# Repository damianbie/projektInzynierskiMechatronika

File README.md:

# Projekt Inżynierski z Mechatroniki

## struktura katalogów

- raport - raport projektu
- algorytm - implementacją algorytmu A i środowiska testowewgo
- robot - projekt fizycznego rogota
    - cady - proejkt cad robota
    - pcbV2 - projekt płytki w programie kiCad
    - soft - oprogramowanie robota napisane w C++ i IDF4.4

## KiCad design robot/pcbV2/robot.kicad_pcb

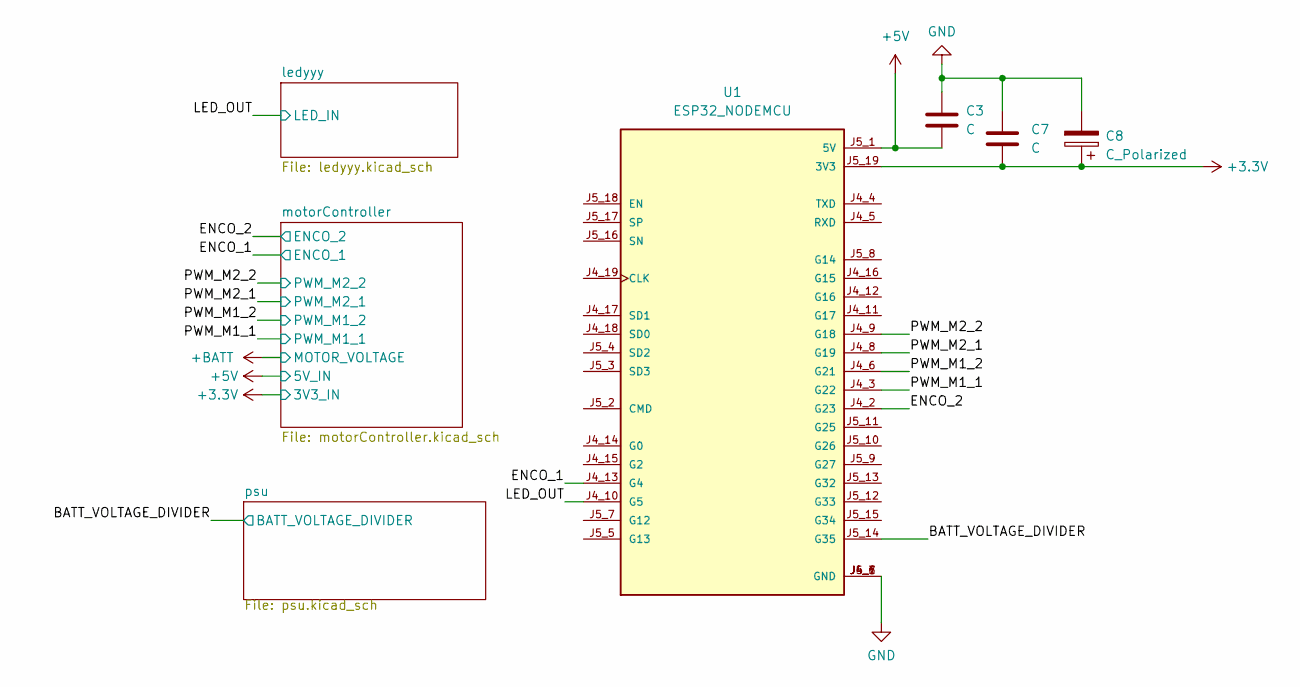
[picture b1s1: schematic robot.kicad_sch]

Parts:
C3, C7: C; C_1210_3225Metric
C8: C_Polarized; CP_Elec_6.3x7.7
U1: ESP32_NODEMCU; MODULE_ESP32_NODEMCU

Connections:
+3.3V: C7.2, C8.1, U1.J5_19 (3V3); also elsewhere on the board
+5V: C3.2, U1.J5_1 (5V); also elsewhere on the board
-BATT: C3.1, C7.1, C8.2, U1.J4_1 (GND), U1.J4_7 (GND), U1.J5_6 (GND); also elsewhere on the board
/BATT_VOLTAGE_DIVIDER: U1.J5_14 (G35); also elsewhere on the board
/ENCO_1: U1.J4_13 (G4); also elsewhere on the board
/ENCO_2: U1.J4_2 (G23); also elsewhere on the board
/LED_OUT: U1.J4_10 (G5); also elsewhere on the board
/PWM_M1_1: U1.J4_3 (G22); also elsewhere on the board
/PWM_M1_2: U1.J4_6 (G21); also elsewhere on the board
/PWM_M2_1: U1.J4_8 (G19); also elsewhere on the board
/PWM_M2_2: U1.J4_9 (G18); also elsewhere on the board

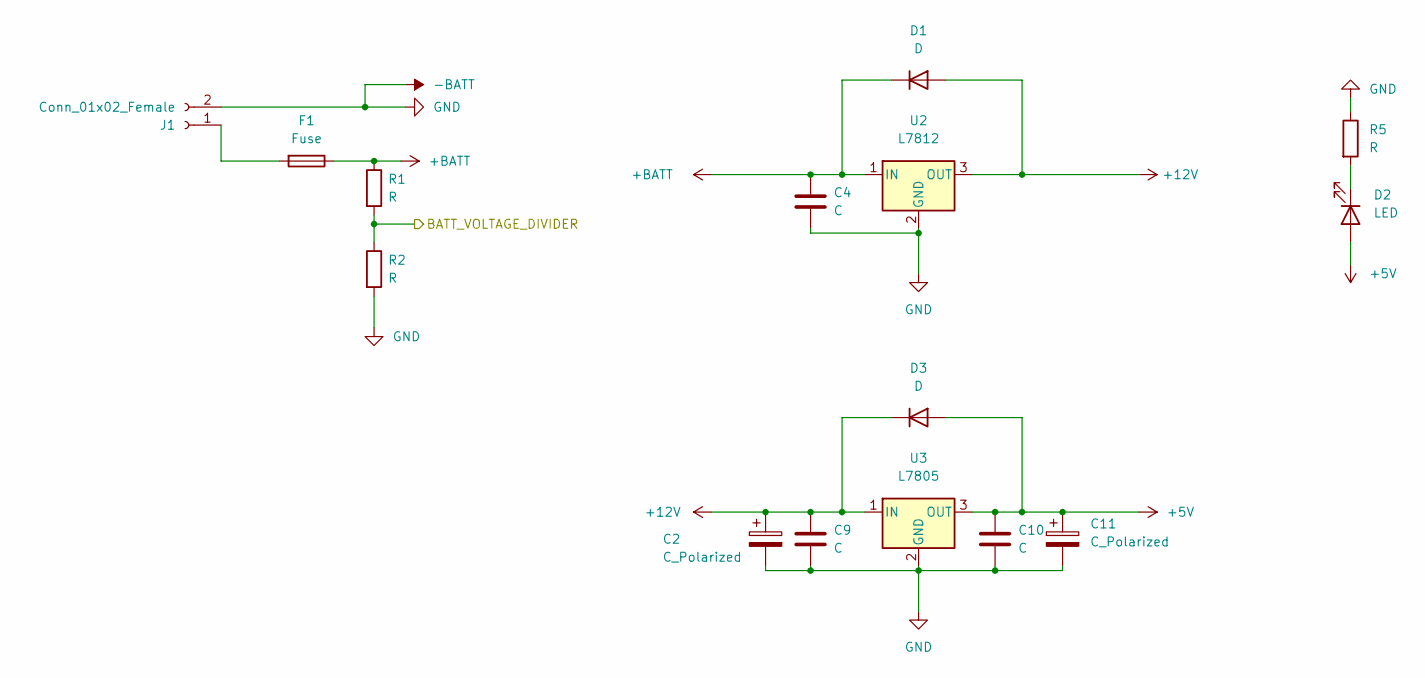
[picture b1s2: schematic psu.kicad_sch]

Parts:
C2, C11: C_Polarized; CP_Elec_6.3x7.7
C4, C9, C10: C; C_1210_3225Metric
D1, D3: D; D_1210_3225Metric
D2: LED; LED_D3.0mm
F1: Fuse; Fuse_1210_3225Metric_Pad1.42x2.65mm_HandSolder
J1: Conn_01x02_Female; TerminalBlock_bornier-2_P5.08mm
R1, R2, R5: R; R_Axial_DIN0207_L6.3mm_D2.5mm_P10.16mm_Horizontal
U2: L7812; TO-220-3_Vertical
U3: L7805; TO-252-2

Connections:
+5V: C10.1, C11.1, D2.2 (A), D3.2 (A), U3.3 (OUT); also elsewhere on the board
+12V: C2.1, C9.1, D1.2 (A), D3.1 (K), U2.3 (OUT), U3.1 (IN)
+BATT: C4.1, D1.1 (K), F1.1, R1.1, U2.1 (IN); also elsewhere on the board
-BATT: C2.2, C4.2, C9.2, C10.2, C11.2, J1.2, R2.2, R5.1, U2.2 (GND), U3.2 (GND); also elsewhere on the board
/BATT_VOLTAGE_DIVIDER: R1.2, R2.1; also elsewhere on the board
unnamed: D2.1 (K), R5.2
unnamed: F1.2, J1.1

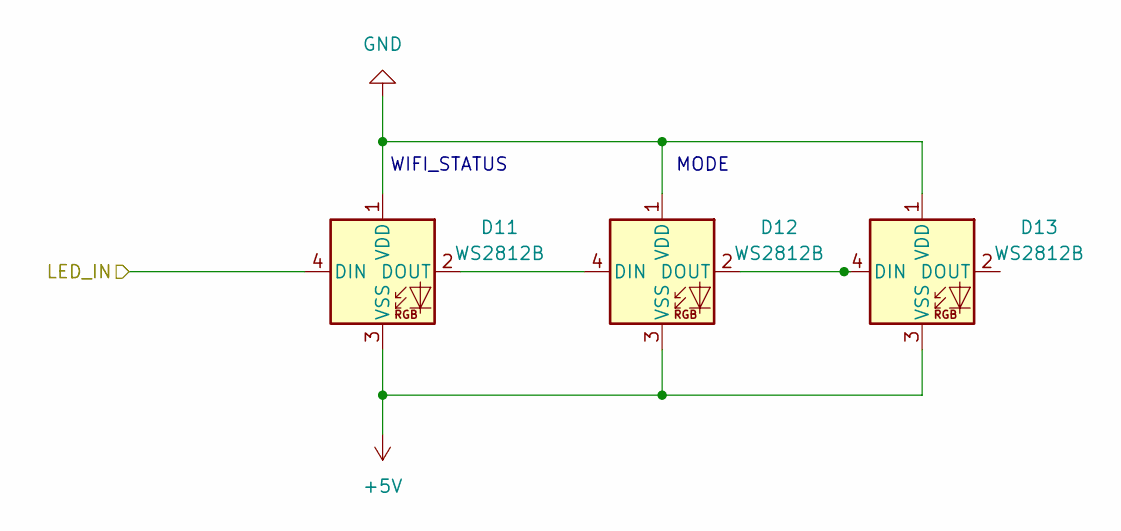
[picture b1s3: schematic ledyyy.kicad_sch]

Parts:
D11, D12, D13: WS2812B; LED_WS2812B_PLCC4_5.0x5.0mm_P3.2mm

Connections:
+5V: D11.3 (VSS), D12.3 (VSS), D13.3 (VSS); also elsewhere on the board
-BATT: D11.1 (VDD), D12.1 (VDD), D13.1 (VDD); also elsewhere on the board
/LED_OUT: D11.4 (DIN); also elsewhere on the board
unnamed: D11.2 (DOUT), D12.4 (DIN)
unnamed: D12.2 (DOUT), D13.4 (DIN)

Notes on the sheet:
WIFI_STATUS
MODE

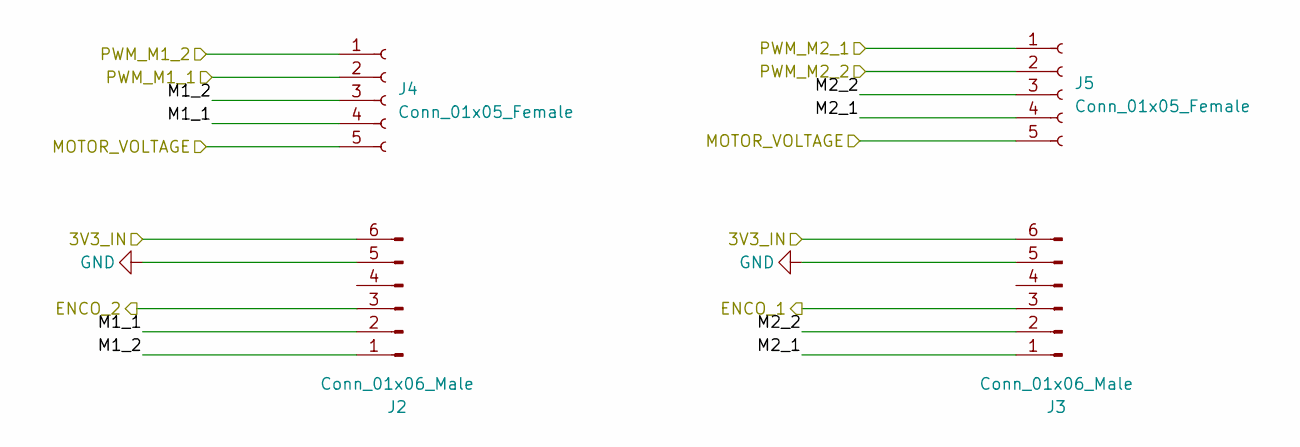
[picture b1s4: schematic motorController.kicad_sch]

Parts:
J2, J3: Conn_01x06_Male; Hirose_DF13C_CL535-0406-3-51_1x06-1MP_P1.25mm_Vertical
J4, J5: Conn_01x05_Female; SolderWire-0.75sqmm_1x05_P4.8mm_D1.25mm_OD2.3mm

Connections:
+3.3V: J2.6, J3.6; also elsewhere on the board
+BATT: J4.5, J5.5; also elsewhere on the board
-BATT: J2.5, J3.5; also elsewhere on the board
/ENCO_1: J3.3; also elsewhere on the board
/ENCO_2: J2.3; also elsewhere on the board
/PWM_M1_1: J4.2; also elsewhere on the board
/PWM_M1_2: J4.1; also elsewhere on the board
/PWM_M2_1: J5.1; also elsewhere on the board
/PWM_M2_2: J5.2; also elsewhere on the board
/motorController/M1_1: J2.2, J4.4
/motorController/M1_2: J2.1, J4.3
/motorController/M2_1: J3.1, J5.4
/motorController/M2_2: J3.2, J5.3

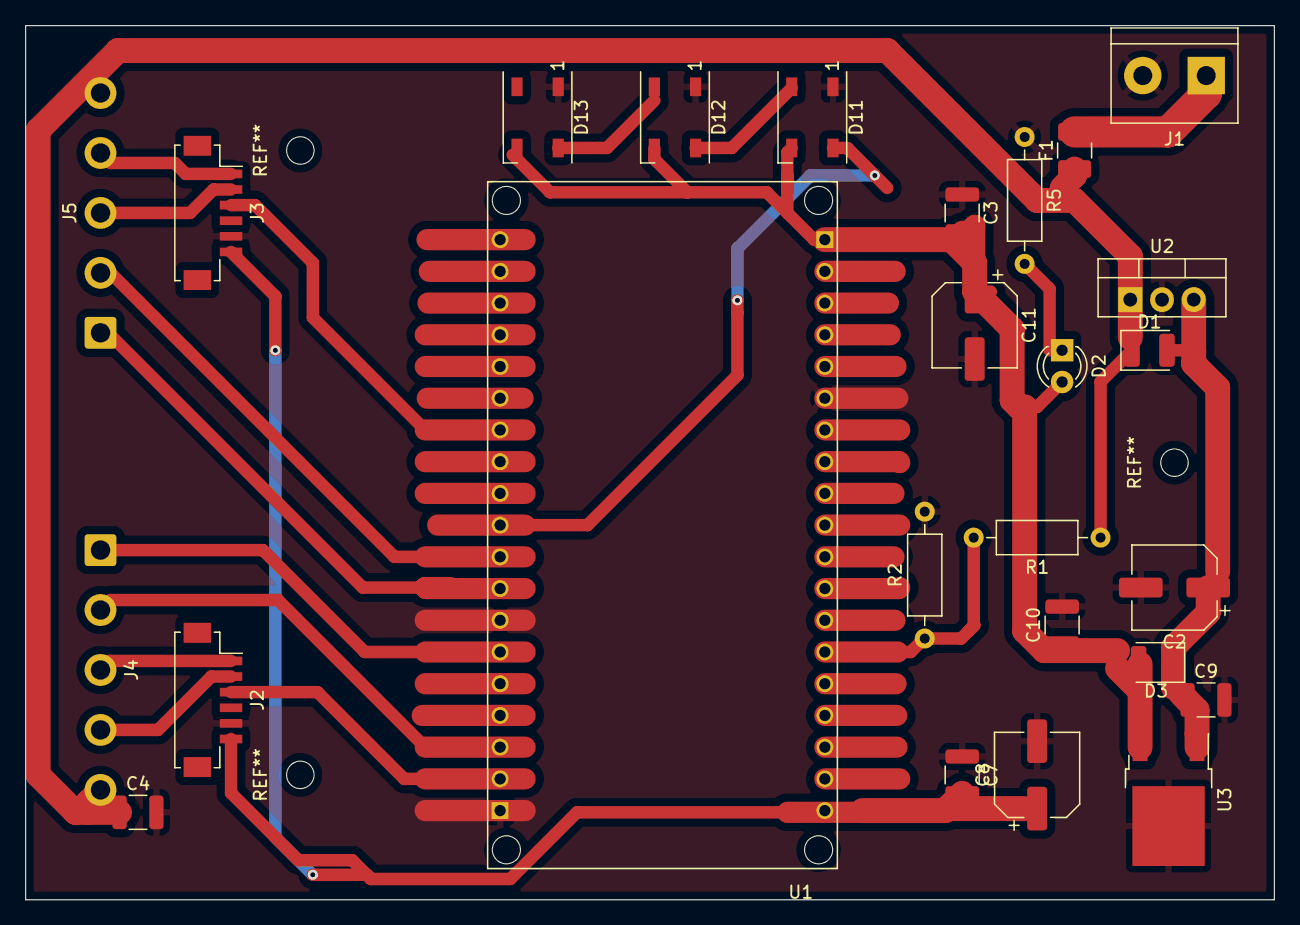
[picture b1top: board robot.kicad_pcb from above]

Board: 2 copper layers, 100.0 x 70.0 mm, 26 parts (0 on the bottom side), 21 nets.

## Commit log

2022-11-28 ver 0.5
2022-12-26 zmiany
2023-01-03 wstepny opis projektu
2023-01-04 dopisany tekst w latexie
2023-01-04 dodanie symulacji przejscia po sciezce przez robota
2023-01-04 dodanie polaczenia z robotem
2023-01-04 przeniesienie folderow
2023-01-04 dodanie wprowadzenia i uporzadkowanie struktury katalogow
2023-01-04 kopia kicad
2023-01-05 dopisane opisu algorytmi i imple,emtacji
2023-01-05 gitignore dla kopii zapasowych
2023-01-06 aktualizacja raportu
2023-01-06 predkosc robota w symulacji pobierana z pliku
2023-01-06 robot
2023-01-06 aktulizacja .gitignore
2023-01-06 nowe rozdzialy
2023-01-06 nowa mapa 35x35
2023-01-06 tytul pdfa, wylaczenie kolorow linkow
2023-01-07 poprawa literowek
2023-01-07 Zmieniono geometrię strony (lepiej wygląda tekst i obrazki), dodano pakiet changes (raport.sty) do wprowadzania zmian, zmieniono wstęp oraz opiekuna pracy
2023-01-10 literowki, przecinki itp
2023-01-10 zmienieony opis elektroniki i modelu, uproszczone schematy w kicadzie
2023-01-10 dodane zdjecie robota
2023-01-10 uproszczony schemat
2023-01-10 aktualizacja
2023-01-10 dodanie opisu innych algorytmow RRT i SLAM
2023-01-10 usuniecie streszczen na koncu
2023-01-11 uzupelnienie testow
2023-01-13 podsumowanie:
2023-01-18 poprawy w raporcie
2023-01-18 cad robota
2023-01-18 testy
